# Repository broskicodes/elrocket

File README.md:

# Manifesto

I believe that anybody who wants to should be able to build rockets in their garage. 

I'm not talking about shitty cardboard rockets that you can buy on Amazon. I mean real intelligent rocket systems capable of actually getting to space (or at least high into the atmosphere).

The goal of this repository is to help make that possible. I want to build a community where people come to share their designs, get inspired and learn from each other.

I'm new to the rocketry scene, but I intend to learn quickly. I will try to document my entire journey right here. All of my designs, code and schematics will live here, open-source, for anybody to use or improve upon.

Enjoy.

## Repo Structure
All designs related to my rocket projects will live here. Everything from CAD files, to PCB designs to code for flight computers (once I get there).

The structure will likely evolve over time, but for now I'm thinking something like this:
- Root directory (You are here)
	- Rockets folder
		- A list of rocket projects I've worked on
		- Each entry will be a folder containing files for that particular project
	- Satellites folder
		- A intend to design and develop satellites at some point too

## Contribution
I am just one person, and I'd love for this to be a community effort.

If you'd like to share your designs here please reach out to me at [braeden@brhall.dev](mailto:braeden@brhall.dev) or just make a PR :)

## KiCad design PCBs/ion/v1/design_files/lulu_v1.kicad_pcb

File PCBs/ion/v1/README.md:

# Ion v1 (prev Lulu)

Design files [here](design_files/).

## Design
Most components and design choices on this board are the same as on [Lulu v0](../v0/README.md).

Core changes include:
- Different MCU
- Added Bluetooth chip
- Removed inputs for servos

Full write up describing changes coming soon.

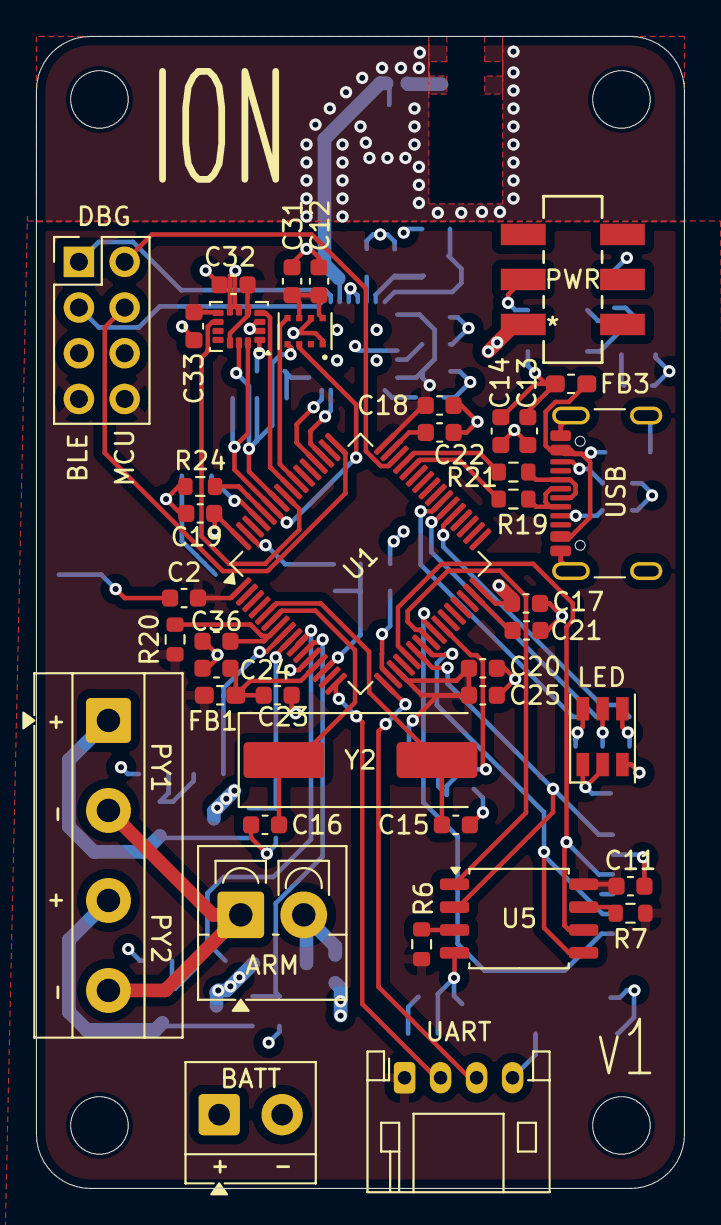
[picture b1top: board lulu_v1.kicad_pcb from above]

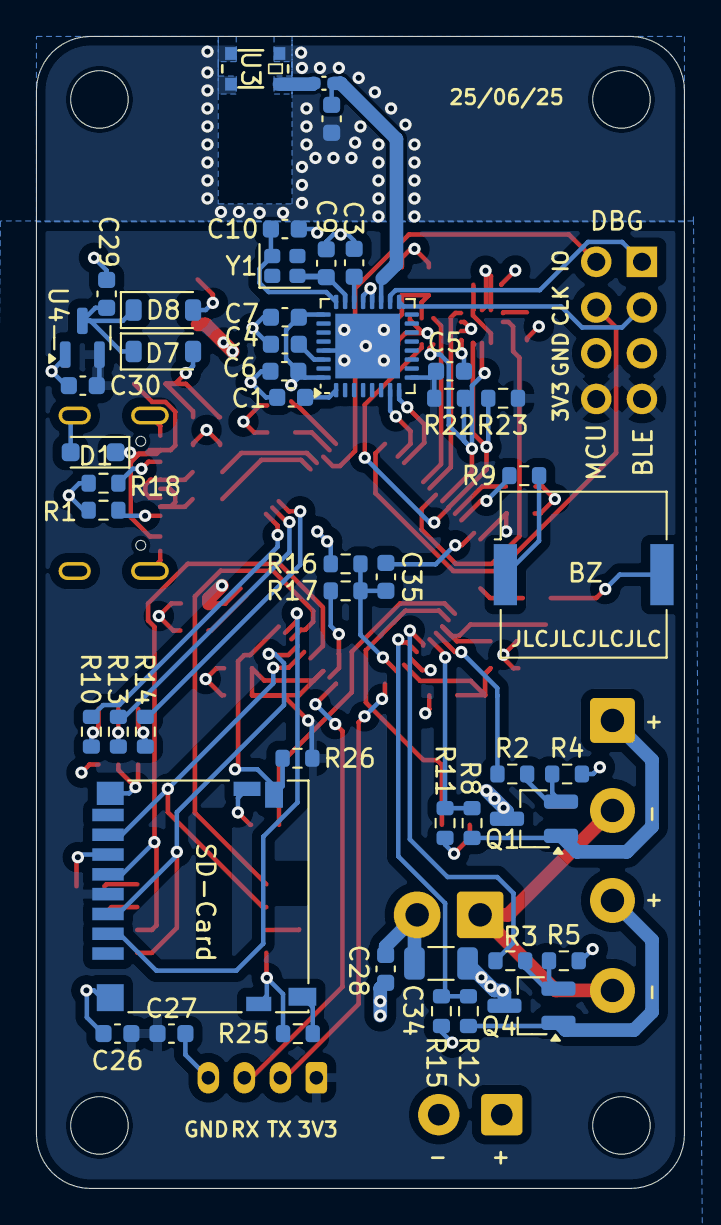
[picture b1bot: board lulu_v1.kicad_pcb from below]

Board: 4 copper layers, 36.0 x 64.0 mm, 89 parts (48 on the bottom side), 67 nets.

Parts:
ARM: SW_SPST; TerminalBlock_4Ucon_1x02_P3.50mm_Vertical
BATT: Battery_Cell; TerminalBlock_MetzConnect_Type059_RT06302HBWC_1x02_P3.50mm_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
BLE: Conn_02x04_Odd_Even; PinHeader_2x04_P2.54mm_Vertical
BZ: Buzzer; Buzzer_Murata_PKMCS0909E
C1, C2, C5, C7, C11, C12, C14, C17, C18, C19, C20, C21, C22, C24, C26, C31, C32, C33, C35, C36: 100nF; C_0603_1608Metric
C3: 100pF; C_0603_1608Metric
C4, C23, C28, C29: 1uF; C_0603_1608Metric
C6, C13, C25, C30: 4.7uF; C_0603_1608Metric
C8: 0.8pF; C_0603_1608Metric
C9, C10: 6pF; C_0603_1608Metric
C15, C16: 20pF; C_0603_1608Metric
C27: 10uF; C_0603_1608Metric
C34: 100uF; C_1206_3216Metric
D1: D_TVS; D_SOD-323_HandSoldering
D7, D8: D_Schottky; D_SOD-123
FB1, FB3: 600@100MHz; L_0603_1608Metric_Pad1.05x0.95mm_HandSolder
L1: 3.9nH; L_0402_1005Metric_Pad0.77x0.64mm_HandSolder
LED: CLX6F-FKC; LED_RGB_PLCC-6
PWR: SW_Slide_DPDT; SW_DPDT
PY1: Screw_Terminal_01x04; TerminalBlock_MetzConnect_Type055_RT01504HDWU_1x04_P5.00mm_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
Q1, Q4: NMOS; SOT-23_Handsoldering
R1, R18: 5.1k; R_0603_1608Metric
R2, R3: 220; R_0603_1608Metric
R4, R5, R6, R7, R17, R20, R22, R23, R24, R25, R26: 10k; R_0603_1608Metric
R8, R12: 8.2k; R_0603_1608Metric
R9, R10: 100; R_0603_1608Metric
R11, R15: 1.8k; R_0603_1608Metric
R13, R14: 68; R_0603_1608Metric
R16: 39k; R_0603_1608Metric
R19, R21: 22; R_0603_1608Metric
SD-Card: Micro_SD_Card_Det_Hirose_DM3AT; microSD_HC_Hirose_DM3D-SF
U1: STM32F405RGTx; LQFP-64_10x10mm_P0.5mm
U2: nRF52810-QCxx; QFN-32-1EP_5x5mm_P0.5mm_EP3.6x3.6mm
U3: 2450AT18D0100E; 2450AT18D0100E_JOT
U4: MCP1702x-330xxTT; SOT-23
U5: W25Q16JVSS; SOIC-8_5.3x5.3mm_P1.27mm
U8: DPS368XTSA1; XDCR_DPS368XTSA1
U9: LSM6DSV80; LGA-14_3x2.5mm_P0.5mm_LayoutBorder3x4y
UART: Conn_01x04_Pin; JST_PH_S4B-PH-K_1x04_P2.00mm_Horizontal
USB: USB_C_Receptacle_USB2.0_16P; USB_C_Receptacle_GCT_USB4105-xx-A_16P_TopMnt_Horizontal
Y1: 32MHz; Crystal_SMD_2016-4Pin_2.0x1.6mm
Y2: 8MHz; Crystal_SMD_HC49-SD

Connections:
3V3_SW: D8.2 (A), PWR.5 (B)
+3.3V: BLE.7, BLE.8, C2.2, C5.1, C6.1, C7.1, C11.1, C12.1, C17.1, C18.1, C19.1, C20.1, C25.2, C26.1, C27.1, C30.1, C31.1, C32.1, C33.1, FB1.2, R6.1, R7.1, R20.1, R22.1, R23.2, R26.1, SD-Card.4 (VDD), U1.1 (VBAT), U1.19 (VDD), U1.32 (VDD), U1.48 (VDD), U1.64 (VDD), U2.9 (VDD), U2.25 (VDD), U2.32 (VDD), U4.2 (VO), U5.8 (VCC), U8.6 (VDDIO), U8.8 (VDD), U9.5 (VDDIO), U9.8 (VDD), U9.12 (CS), UART.1
+BATT: ARM.2 (B), BATT.1 (+), C28.1, C34.1, PWR.6 (C), R16.1
+VBUS: C13.1, C14.1, D7.2 (A), FB3.1
BAR_EXTI: U1.55 (PB3), U8.5 (SDO)
BATT_VOLT: C35.1, R16.2, R17.1, U1.14 (PA0)
BLE_SWDCLK: BLE.3, U2.17 (SWDCLK)
BLE_SWDIO: BLE.1, U2.18 (SWDIO)
BLE_UART_RX: U1.52 (PC11), U2.8 (P0.10)
BLE_UART_TX: U1.51 (PC10), U2.7 (P0.09)
BUZZER: R9.1, U1.61 (PB8)
B_PWM: R14.1, U1.39 (PC8)
CS_FM: U1.24 (PC4), U5.1 (~CS)
CS_SD: SD-Card.2 (DAT3/CD), U1.25 (PC5)
DET_B: R26.2, SD-Card.9 (DET_B), U1.26 (PB0)
DM: R19.2, U1.44 (PA11)
DP: R21.2, U1.45 (PA12)
GND: BATT.2 (-), BLE.5, BLE.6, BZ.2 (-), C1.1, C2.1, C3.1, C4.1, C5.2, C6.2, C7.2, C8.2, C9.1, C10.1, C11.2, C12.2, C13.2, C14.2, C15.2, C16.2, C17.2, C18.2, C19.2, C20.2, C21.2, C22.2, C23.2, C24.1, C25.1, C26.2, C27.2, C28.2, C29.2, C30.2, C31.2, C32.2, C33.2, C34.2, C35.2, C36.1, D1.2 (A2), LED.1 (KB), LED.2 (KG), LED.3 (KR), Q1.3 (S), Q4.3 (S), R1.2, R4.2, R5.2, R11.2, R15.2, R17.2, R18.2, R24.1, R25.1, SD-Card.6 (VSS), SD-Card.11 (SHIELD), U1.12 (VSSA), U1.18 (VSS), U1.63 (VSS), U2.20 (VSS), U2.21 (DEC2), U2.29 (VSS), U2.33 (VSS), U3.1 (FEED), U3.2 (GND), U3.3 (GND), U4.1 (GND), U5.4 (GND), U8.1 (GND), U8.7 (GND__1), U9.1 (SDO/TA0), U9.2 (SDX), U9.3 (SCX), U9.6 (GND), U9.7 (GND), UART.4, USB.A1 (GND), USB.A12 (GND), USB.B1 (GND), USB.B12 (GND), USB.S1 (SHIELD)
G_PWM: R13.2, U1.38 (PC7)
IMU_EXTI1: U1.56 (PB4), U9.4 (INT1)
IMU_EXTI2: U1.57 (PB5), U9.9 (INT2)
LORA_UART_RX: U1.17 (PA3), UART.3
LORA_UART_TX: U1.16 (PA2), UART.2
MCU_SWDCLK: BLE.4, U1.49 (PA14)
MCU_SWDIO: BLE.2, U1.46 (PA13)
MISO: SD-Card.7 (DAT0), U1.22 (PA6), U5.2 (DO/IO_{1})
MOSI: SD-Card.3 (CMD), U1.23 (PA7), U5.5 (DI/IO_{0})
unnamed: BZ.1 (+), R9.2
unnamed: D1.1 (A1), FB3.2, USB.A4 (VBUS), USB.A9 (VBUS), USB.B4 (VBUS), USB.B9 (VBUS)
unnamed: LED.6 (AB), R14.2
unnamed: LED.5 (AG), R13.1
unnamed: LED.4 (AR), R10.1
unnamed: C29.1, D7.1 (K), D8.1 (K), U4.3 (VI)
unnamed: R1.1, USB.A5 (CC1)
unnamed: R18.1, USB.B5 (CC2)
unnamed: R21.1, USB.A6 (D+), USB.B6 (D+)
unnamed: R19.1, USB.A7 (D-), USB.B7 (D-)
unnamed: PY1.1, Q1.1 (D), R8.1
unnamed: ARM.1 (A), PY1.2, PY1.4
unnamed: R25.2, SD-Card.10 (DET_A)
unnamed: Q1.2 (G), R2.2, R4.1
unnamed: Q4.2 (G), R3.2, R5.1
unnamed: R24.2, U1.60 (BOOT0)
unnamed: C36.2, R20.2, U1.7 (NRST)
unnamed: C21.1, U1.31 (VCAP_1)
unnamed: C22.1, U1.47 (VCAP_2)
unnamed: C23.1, C24.2, FB1.1, U1.13 (VDDA)
unnamed: C8.1, L1.2, U2.19 (ANT)
unnamed: C1.2, U2.1 (DEC1)
unnamed: C3.2, U2.22 (DEC3)
unnamed: C4.2, U2.30 (DEC4)
unnamed: C9.2, U2.23 (XC1), Y1.2
unnamed: C10.2, U2.24 (XC2), Y1.1
unnamed: L1.1, U3.4 (FEED_ALT)
unnamed: R7.2, U5.7 (~HOLD/~RESET/IO_{3})
unnamed: R6.2, U5.3 (~WP/IO_{2})
PY1: R2.1, U1.8 (PC0)
PY1_CONT: R8.2, R11.1, U1.9 (PC1)
PY2: R3.1, U1.10 (PC2)
PY2_CONT: R12.2, R15.1, U1.11 (PC3)
PY2_N: PY1.3, Q4.1 (D), R12.1
R_PWM: R10.2, U1.37 (PC6)
SCK: SD-Card.5 (CLK), U1.21 (PA5), U5.6 (CLK)
SCL: R22.2, U1.58 (PB6), U8.4 (SCK), U9.13 (SCL)
SDA: R23.1, U1.59 (PB7), U8.3 (SDI), U9.14 (SDA)
XIN: C15.1, U1.5 (PH0), Y2.2
XOUT: C16.1, U1.6 (PH1), Y2.1

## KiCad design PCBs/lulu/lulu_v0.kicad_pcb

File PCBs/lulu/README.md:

# Lulu

Lulu is a flight computer. I am designing her to be simple and small. The primary goal of the computer is to record and log flight data from sensors for analysis and testing.

The [v0](v0/) design of Lulu is complete, but not going into production (click to find out [why](v0/README.md#limitations)). I will start work on v1 redesign soon.

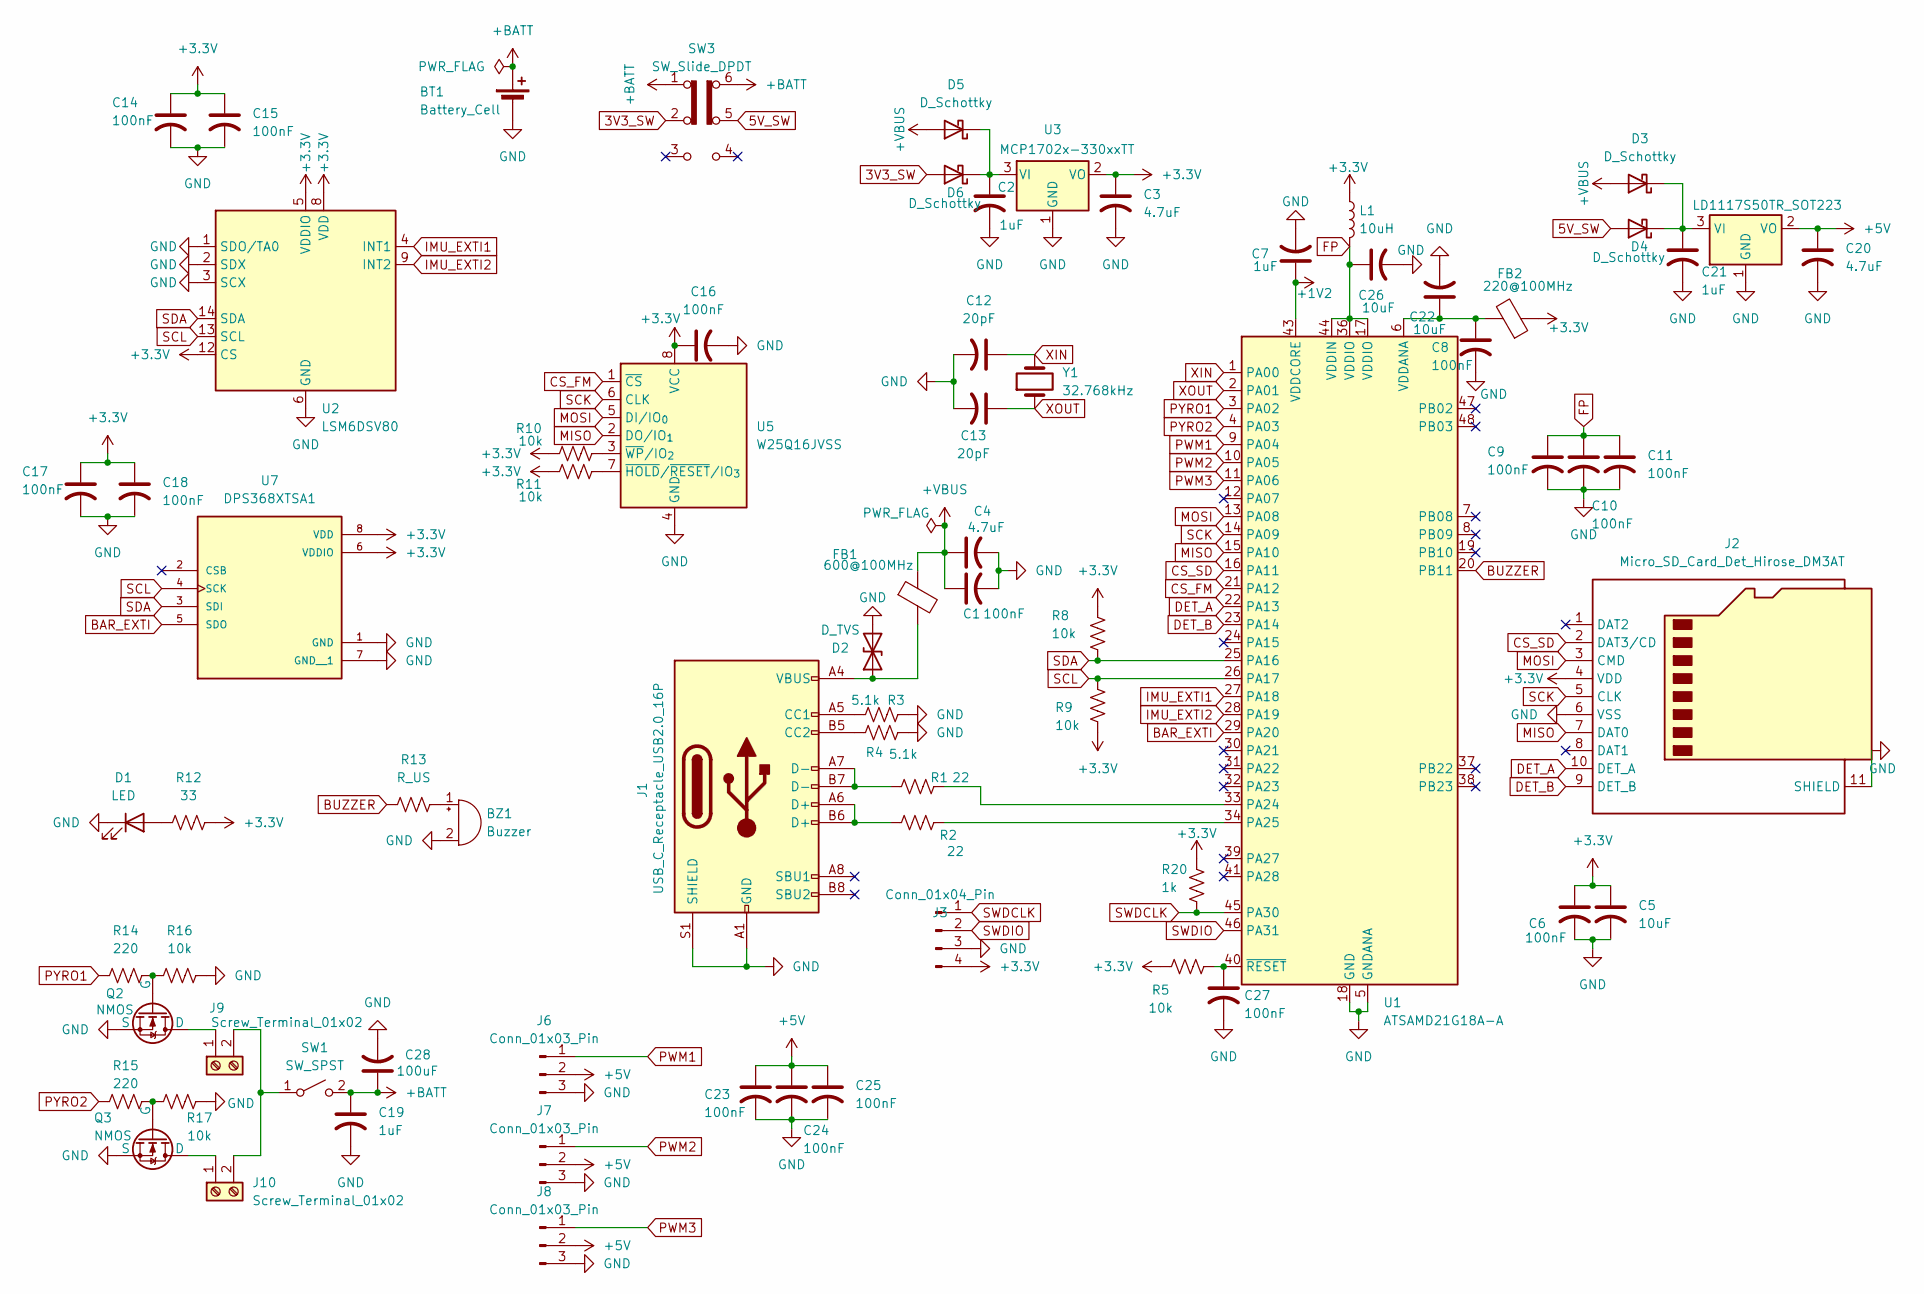
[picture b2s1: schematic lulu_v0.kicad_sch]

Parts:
BT1: Battery_Cell; TerminalBlock_MetzConnect_Type055_RT01502HDWU_1x02_P5.00mm_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
BZ1: Buzzer; Buzzer_Murata_PKMCS0909E
C1, C6, C8, C9, C10, C11, C14, C15, C16, C17, C18, C23, C24, C25, C27: 100nF; C_0603_1608Metric
C2, C7, C19, C21: 1uF; C_0603_1608Metric
C3, C4, C20: 4.7uF; C_0603_1608Metric
C5, C22, C26: 10uF; C_0603_1608Metric
C12, C13: 20pF; C_0603_1608Metric
C28: 100uF; C_0603_1608Metric
D1: LED; LED_0805_2012Metric
D2: D_TVS; D_SOD-323_HandSoldering
D3, D4, D5, D6: D_Schottky; D_SOD-123
FB1: 600@100MHz; L_0603_1608Metric_Pad1.05x0.95mm_HandSolder
FB2: 220@100MHz; L_0603_1608Metric_Pad1.05x0.95mm_HandSolder
J1: USB_C_Receptacle_USB2.0_16P; USB_C_Receptacle_GCT_USB4105-xx-A_16P_TopMnt_Horizontal
J2: Micro_SD_Card_Det_Hirose_DM3AT; microSD_HC_Hirose_DM3D-SF
J3: Conn_01x04_Pin; PinHeader_1x04_P2.54mm_Vertical
J6, J7, J8: Conn_01x03_Pin; PinHeader_1x03_P2.54mm_Vertical
J9, J10: Screw_Terminal_01x02; TerminalBlock_MetzConnect_Type055_RT01502HDWU_1x02_P5.00mm_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
L1: 10uH; L_1812_4532Metric_Pad1.30x3.40mm_HandSolder
Q2, Q3: NMOS; SOT-23_Handsoldering
R1, R2: 22; R_0603_1608Metric
R3, R4: 5.1k; R_0603_1608Metric
R5, R8, R9, R10, R11, R16, R17: 10k; R_0603_1608Metric
R12: 33; R_0603_1608Metric
R13: R_US; R_0603_1608Metric
R14, R15: 220; R_0603_1608Metric
R20: 1k; R_0603_1608Metric
SW1: SW_SPST; TerminalBlock_4Ucon_1x02_P3.50mm_Vertical
SW3: SW_Slide_DPDT; SW_DPDT
U1: ATSAMD21G18A-A; TQFP-48_7x7mm_P0.5mm
U2: LSM6DSV80; LGA-14_3x2.5mm_P0.5mm_LayoutBorder3x4y
U3: MCP1702x-330xxTT; SOT-23
U5: W25Q16JVSS; SOIC-8_5.3x5.3mm_P1.27mm
U6: LD1117S50TR_SOT223; SOT-223-3_TabPin2
U7: DPS368XTSA1; XDCR_DPS368XTSA1
Y1: 32.768kHz; Crystal_SMD_MicroCrystal_CC7V-T1A-2Pin_3.2x1.5mm_HandSolder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

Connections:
3V3_SW: D6.2 (A), SW3.2 (B)
5V_SW: D4.2 (A), SW3.5 (B)
+1V2: C7.1, U1.43 (VDDCORE)
+3.3V: C3.1, C5.1, C6.1, C14.1, C15.1, C16.1, C17.1, C18.1, FB2.1, J2.4 (VDD), J3.4, L1.1, R5.1, R8.1, R9.2, R10.1, R11.1, R12.2, R20.1, U2.5 (VDDIO), U2.8 (VDD), U2.12 (CS), U3.2 (VO), U5.8 (VCC), U7.6 (VDDIO), U7.8 (VDD)
+5V: C20.1, C23.1, C24.1, C25.1, J6.2, J7.2, J8.2, U6.2 (VO)
+BATT: BT1.1 (+), C19.1, C28.1, SW1.2 (B), SW3.1 (A), SW3.6 (C); also elsewhere on the board
+VBUS: C1.1, C4.1, D3.2 (A), D5.2 (A), FB1.1
BAR_EXTI: U1.29 (PA20), U7.5 (SDO)
BUZZER: R13.1, U1.20 (PB11)
CS_FM: U1.21 (PA12), U5.1 (~CS)
CS_SD: J2.2 (DAT3/CD), U1.16 (PA11)
DET_A: J2.10 (DET_A), U1.22 (PA13)
DET_B: J2.9 (DET_B), U1.23 (PA14)
FP: C9.1, C10.1, C11.1, C26.1, L1.2, U1.17 (VDDIO), U1.36 (VDDIO), U1.44 (VDDIN)
GND: BT1.2 (-), BZ1.2 (-), C1.2, C2.2, C3.2, C4.2, C5.2, C6.2, C7.2, C8.2, C9.2, C10.2, C11.2, C12.2, C13.2, C14.2, C15.2, C16.2, C17.2, C18.2, C19.2, C20.2, C21.2, C22.2, C23.2, C24.2, C25.2, C26.2, C27.2, C28.2, D1.1 (K), D2.2 (A2), J1.A1 (GND), J1.A12 (GND), J1.B1 (GND), J1.B12 (GND), J1.S1 (SHIELD), J2.6 (VSS), J2.11 (SHIELD), J3.3, J6.3, J7.3, J8.3, Q2.3 (S), Q3.3 (S), R3.2, R4.2, R16.2, R17.2, U1.5 (GNDANA), U1.18 (GND), U1.35 (GND), U1.42 (GND), U2.1 (SDO/TA0), U2.2 (SDX), U2.3 (SCX), U2.6 (GND), U2.7 (GND), U3.1 (GND), U5.4 (GND), U6.1 (GND), U7.1 (GND), U7.7 (GND__1); also elsewhere on the board
IMU_EXTI1: U1.27 (PA18), U2.4 (INT1)
IMU_EXTI2: U1.28 (PA19), U2.9 (INT2)
MISO: J2.7 (DAT0), U1.15 (PA10), U5.2 (DO/IO_{1})
MOSI: J2.3 (CMD), U1.13 (PA08), U5.5 (DI/IO_{0})
unnamed: BZ1.1 (+), R13.2
unnamed: D1.2 (A), R12.1
unnamed: D2.1 (A1), FB1.2, J1.A4 (VBUS), J1.A9 (VBUS), J1.B4 (VBUS), J1.B9 (VBUS)
unnamed: C21.1, D3.1 (K), D4.1 (K), U6.3 (VI)
unnamed: C2.1, D5.1 (K), D6.1 (K), U3.3 (VI)
unnamed: J1.A5 (CC1), R3.1
unnamed: J1.B5 (CC2), R4.1
unnamed: J1.A6 (D+), J1.B6 (D+), R2.1
unnamed: J1.A7 (D-), J1.B7 (D-), R1.1
unnamed 28: J9.1, Q2.1 (D); also elsewhere on the board
unnamed 29: J10.1, Q3.1 (D); also elsewhere on the board
unnamed 30: J9.2, J10.2, SW1.1 (A); also elsewhere on the board
unnamed: Q2.2 (G), R14.2, R16.1
unnamed: Q3.2 (G), R15.2, R17.1
unnamed: R1.2, U1.33 (PA24)
unnamed: R2.2, U1.34 (PA25)
unnamed: C8.1, C22.1, FB2.2, U1.6 (VDDANA)
unnamed: C27.1, R5.2, U1.40 (~RESET)
unnamed: R11.2, U5.7 (~HOLD/~RESET/IO_{3})
unnamed: R10.2, U5.3 (~WP/IO_{2})
PWM1: J6.1, U1.9 (PA04)
PWM2: J7.1, U1.10 (PA05)
PWM3: J8.1, U1.11 (PA06)
PYRO1: R14.1, U1.3 (PA02)
PYRO2: R15.1, U1.4 (PA03)
SCK: J2.5 (CLK), U1.14 (PA09), U5.6 (CLK)
SCL: R9.1, U1.26 (PA17), U2.13 (SCL), U7.4 (SCK)
SDA: R8.2, U1.25 (PA16), U2.14 (SDA), U7.3 (SDI)
SWDCLK: J3.1, R20.2, U1.45 (PA30)
SWDIO: J3.2, U1.46 (PA31)
XIN: C12.1, U1.1 (PA00), Y1.2
XOUT: C13.1, U1.2 (PA01), Y1.1

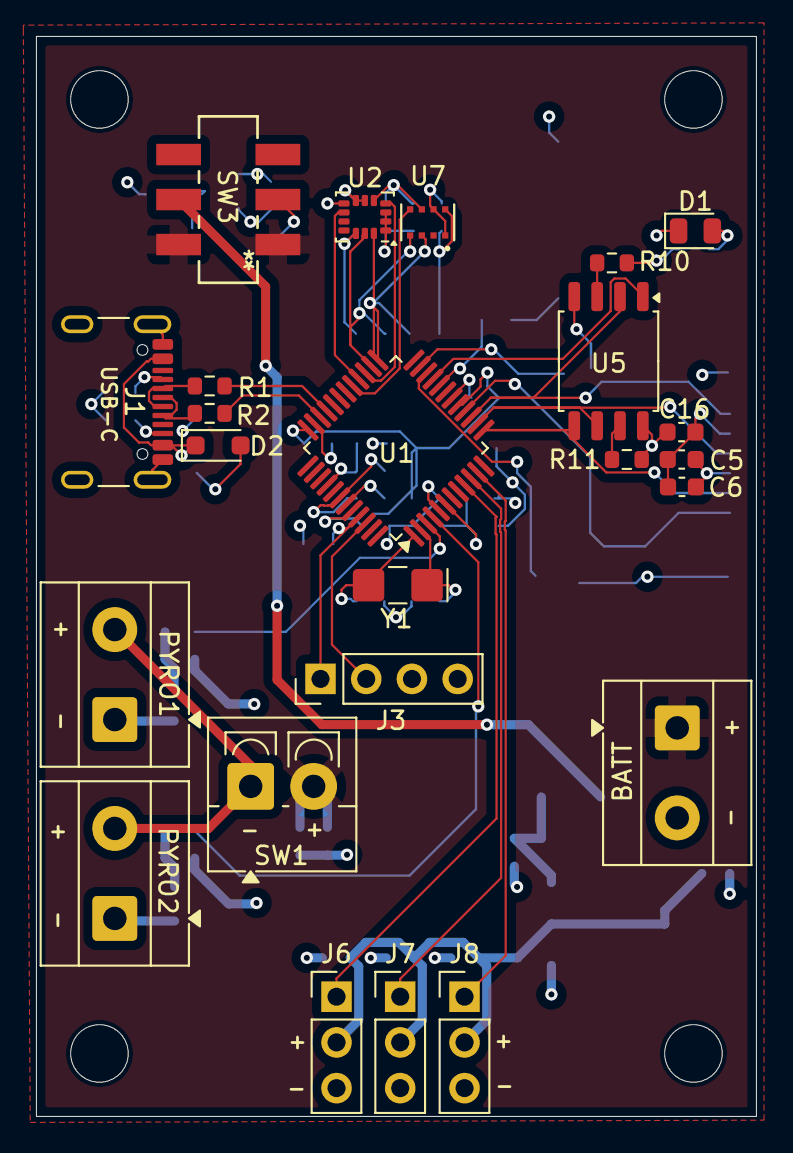
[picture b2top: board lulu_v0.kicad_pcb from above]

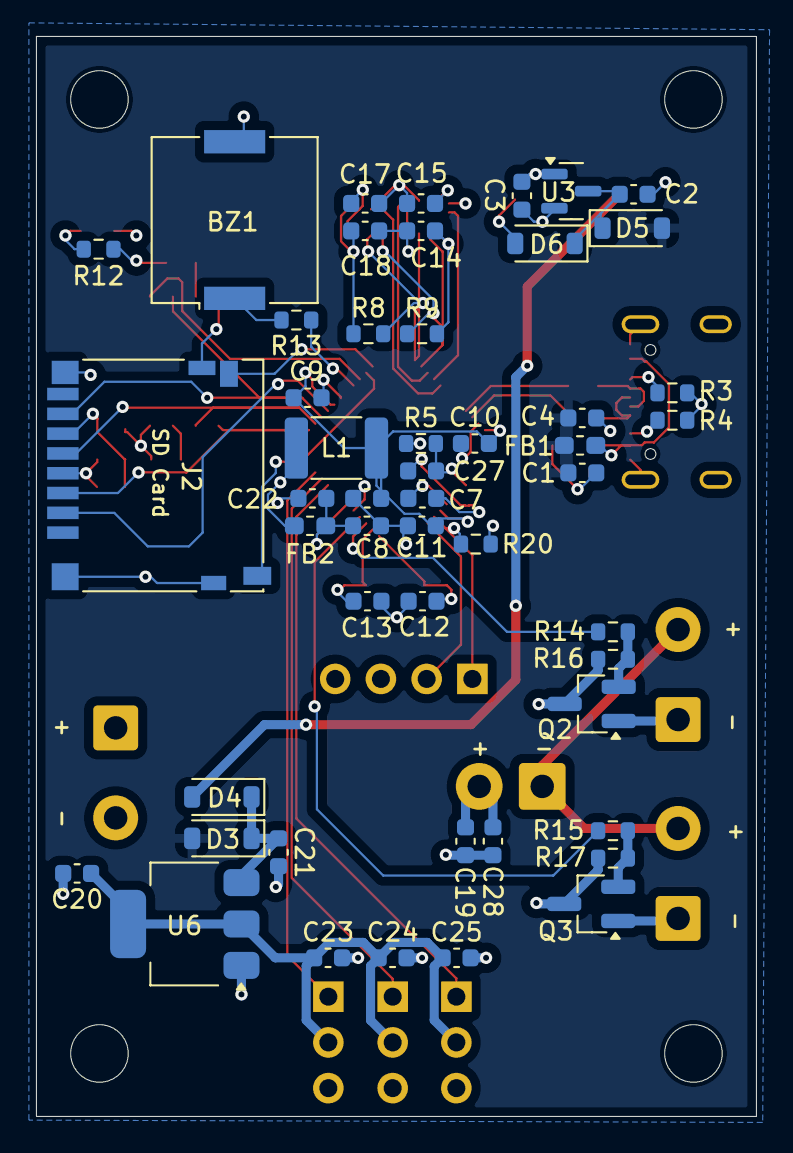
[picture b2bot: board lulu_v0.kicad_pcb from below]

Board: 4 copper layers, 40.0 x 60.0 mm, 74 parts (50 on the bottom side), 51 nets.

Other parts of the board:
BATT: Battery_Cell; TerminalBlock_MetzConnect_Type055_RT01502HDWU_1x02_P5.00mm_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
PYRO1, PYRO2: Screw_Terminal_01x02; TerminalBlock_MetzConnect_Type055_RT01502HDWU_1x02_P5.00mm_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

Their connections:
+BATT: BATT.1 (+); also elsewhere on the board
GND: BATT.2 (-); also elsewhere on the board
unnamed 28: PYRO1.1; also elsewhere on the board
unnamed 29: PYRO2.1; also elsewhere on the board
unnamed 30: PYRO1.2, PYRO2.2; also elsewhere on the board

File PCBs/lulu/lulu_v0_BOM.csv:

"Reference","Qty","Value","DNP","Exclude from BOM","Exclude from Board","Footprint","Datasheet"
"BT1","1","Battery_Cell","","","","TerminalBlock_MetzConnect:TerminalBlock_MetzConnect_Type055_RT01502HDWU_1x02_P5.00mm_Horizontal","~"
"BZ1","1","Buzzer","","","","Buzzer_Beeper:Buzzer_Murata_PKMCS0909E","~"
"C1,C6,C8,C9,C10,C11,C14,C15,C16,C17,C18,C23,C24,C25,C27","15","100nF","","","","Capacitor_SMD:C_0603_1608Metric",""
"C2,C7,C19,C21","4","1uF","","","","Capacitor_SMD:C_0603_1608Metric",""
"C3,C4,C20","3","4.7uF","","","","Capacitor_SMD:C_0603_1608Metric",""
"C5,C22,C26","3","10uF","","","","Capacitor_SMD:C_0603_1608Metric",""
"C12,C13","2","20pF","","","","Capacitor_SMD:C_0603_1608Metric",""
"C28","1","100uF","","","","Capacitor_SMD:C_0603_1608Metric",""
"D1","1","LED","","","","LED_SMD:LED_0805_2012Metric","~"
"D2","1","D_TVS","","","","Diode_SMD:D_SOD-323_HandSoldering","~"
"D3,D4,D5,D6","4","D_Schottky","","","","Diode_SMD:D_SOD-123","~"
"FB1","1","600@100MHz","","","","Inductor_SMD:L_0603_1608Metric_Pad1.05x0.95mm_HandSolder","~"
"FB2","1","220@100MHz","","","","Inductor_SMD:L_0603_1608Metric_Pad1.05x0.95mm_HandSolder","~"
"J1","1","USB_C_Receptacle_USB2.0_16P","","","","Connector_USB:USB_C_Receptacle_GCT_USB4105-xx-A_16P_TopMnt_Horizontal","https://www.usb.org/sites/default/files/documents/usb_type-c.zip"
"J2","1","Micro_SD_Card_Det_Hirose_DM3AT","","","","Connector_Card:microSD_HC_Hirose_DM3D-SF","https://www.hirose.com/product/en/download_file/key_name/DM3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"
"J3","1","Conn_01x04_Pin","","","","Connector_PinHeader_2.54mm:PinHeader_1x04_P2.54mm_Vertical","~"
"J6,J7,J8","3","Conn_01x03_Pin","","","","Connector_PinHeader_2.54mm:PinHeader_1x03_P2.54mm_Vertical","~"
"J9,J10","2","Screw_Terminal_01x02","","","","TerminalBlock_MetzConnect:TerminalBlock_MetzConnect_Type055_RT01502HDWU_1x02_P5.00mm_Horizontal","~"
"L1","1","10uH","","","","Inductor_SMD:L_1812_4532Metric_Pad1.30x3.40mm_HandSolder","~"
"Q2,Q3","2","NMOS","","","","Package_TO_SOT_SMD:SOT-23_Handsoldering","https://ngspice.sourceforge.io/docs/ngspice-html-manual/manu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"
"R1,R2","2","22","","","","Resistor_SMD:R_0603_1608Metric","~"
"R3,R4","2","5.1k","","","","Resistor_SMD:R_0603_1608Metric","~"
"R5,R8,R9,R10,R11,R16,R17","7","10k","","","","Resistor_SMD:R_0603_1608Metric","~"
"R12","1","33","","","","Resistor_SMD:R_0603_1608Metric","~"
"R13","1","R_US","","","","Resistor_SMD:R_0603_1608Metric","~"
"R14,R15","2","220","","","","Resistor_SMD:R_0603_1608Metric","~"
"R20","1","1k","","","","Resistor_SMD:R_0603_1608Metric","~"
"SW1","1","SW_SPST","","","","TerminalBlock_4Ucon:TerminalBlock_4Ucon_1x02_P3.50mm_Vertical","~"
"SW3","1","SW_Slide_DPDT","","","","SW_DPDT:SW_DPDT","~"
"U1","1","ATSAMD21G18A-A","","","","Package_QFP:TQFP-48_7x7mm_P0.5mm","http://ww1.microchip.com/downloads/en/DeviceDoc/SAM_D21_DA1_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"
"U2","1","LSM6DSV80","","","","Package_LGA:LGA-14_3x2.5mm_P0.5mm_LayoutBorder3x4y","https://mm.digikey.com/Volume0/opasdata/d220001/medias/docus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"
"U3","1","MCP1702x-330xxTT","","","","Package_TO_SOT_SMD:SOT-23","http://ww1.microchip.com/downloads/en/DeviceDoc/20001826D.pdf"
"U5","1","W25Q16JVSS","","","","Package_SO:SOIC-8_5.3x5.3mm_P1.27mm","https://www.winbond.com/hq/support/documentation/levelOne.js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"
"U6","1","LD1117S50TR_SOT223","","","","Package_TO_SOT_SMD:SOT-223-3_TabPin2","http://www.st.com/st-web-ui/static/active/en/resource/techni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"
"U7","1","DPS368XTSA1","","","","DPS368XTSA1:XDCR_DPS368XTSA1",""
"Y1","1","32.768kHz","","","","Crystal:Crystal_SMD_MicroCrystal_CC7V-T1A-2Pin_3.2x1.5mm_HandSoldering","~"

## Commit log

2025-06-12 init
2025-06-12 add structure
2025-06-12 add baptism design files
2025-06-14 baptism readme
2025-06-19 add files for lulu v0
2025-06-19 make v0 dir
2025-06-19 add readme and pics for lulu
2025-06-19 dir for design files
2025-06-19 its kicad
2025-06-20 copper poors
2025-06-25 ion v1
2025-06-26 ion v1 gerbers
2025-06-28 upadted design files
2025-07-14 link to v0
2025-07-14 no grav
2025-07-14 ref ion
2025-07-14 style
